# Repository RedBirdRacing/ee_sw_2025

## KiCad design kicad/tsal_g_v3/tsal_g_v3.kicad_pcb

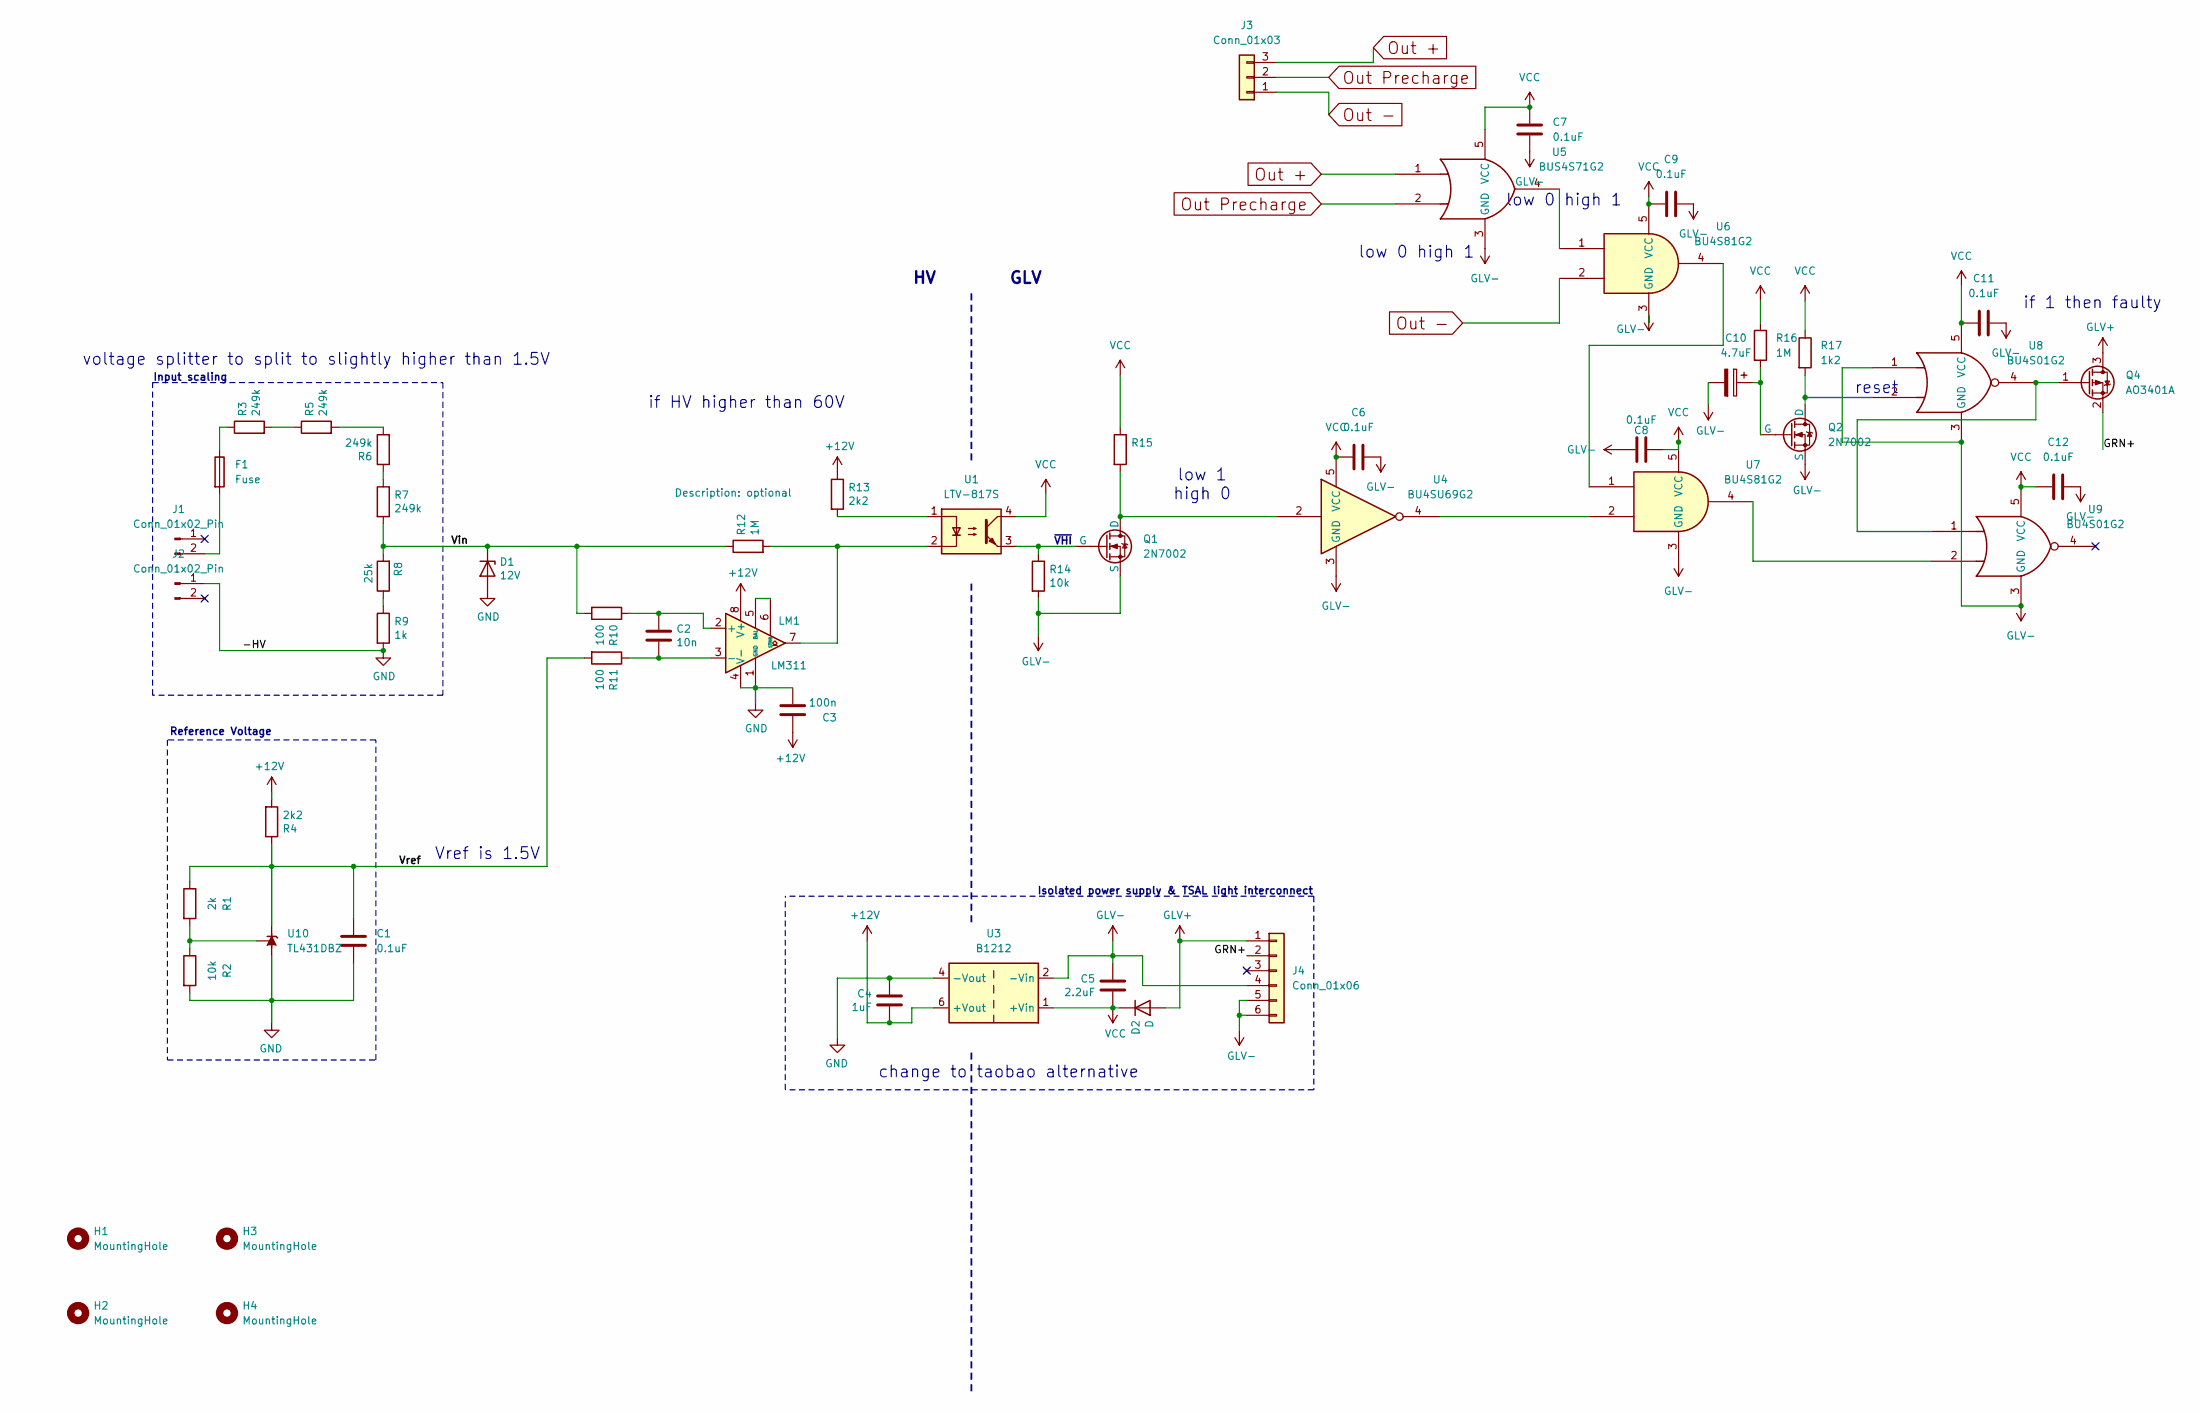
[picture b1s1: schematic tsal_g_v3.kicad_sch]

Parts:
C1, C6, C7, C8, C9, C11, C12: 0.1uF; C_0805_2012Metric_Pad1.18x1.45mm_HandSolder
C2: 10n; C_0805_2012Metric_Pad1.18x1.45mm_HandSolder
C3: 100n; C_0805_2012Metric_Pad1.18x1.45mm_HandSolder
C4: 1uF; C_0805_2012Metric_Pad1.18x1.45mm_HandSolder
C5: 2.2uF; C_0805_2012Metric_Pad1.18x1.45mm_HandSolder
C10: 4.7uF; C_0805_2012Metric_Pad1.18x1.45mm_HandSolder
D1: 12V; D_DO-35_SOD27_P7.62mm_Horizontal
D2: D; D_SMA
F1: Fuse; Fuse_0805_2012Metric_Pad1.15x1.40mm_HandSolder
H1, H2, H3, H4: MountingHole; MountingHole_3.2mm_M3
J1, J2: Conn_01x02_Pin; AMASS_XT60-M_1x02_P7.20mm_Vertical
J3: Conn_01x03; JST_VH_B3P-VH_1x03_P3.96mm_Vertical
J4: Conn_01x06; JST_VH_B6P-VH_1x06_P3.96mm_Vertical
LM1: LM311; SOIC-8_3.9x4.9mm_P1.27mm
Q1, Q2: 2N7002; SOT-23_Handsoldering
Q4: AO3401A; SOT-23_Handsoldering
R1: 2k; R_0805_2012Metric_Pad1.20x1.40mm_HandSolder
R2, R14: 10k; R_0805_2012Metric_Pad1.20x1.40mm_HandSolder
R3, R5, R6, R7: 249k; R_0805_2012Metric_Pad1.20x1.40mm_HandSolder
R4, R13: 2k2; R_0805_2012Metric_Pad1.20x1.40mm_HandSolder
R8: 25k; R_0805_2012Metric_Pad1.20x1.40mm_HandSolder
R9: 1k; R_0805_2012Metric_Pad1.20x1.40mm_HandSolder
R10, R11: 100; R_0805_2012Metric_Pad1.20x1.40mm_HandSolder
R12, R16: 1M; R_0805_2012Metric_Pad1.20x1.40mm_HandSolder
R15: R_0805_2012Metric_Pad1.20x1.40mm_HandSolder
R17: 1k2; R_0805_2012Metric_Pad1.20x1.40mm_HandSolder
U1: LTV-817S; SMDIP-4_W9.53mm
U3: B1212; Converter_DCDC_TRACO_TBA2-xxxx_Single_THT
U4: BU4SU69G2; SOT-23-5_HandSoldering
U5: BUS4S71G2; SOT-23-5_HandSoldering
U6, U7: BU4S81G2; SOT-23-5_HandSoldering
U8, U9: BU4S01G2; SOT-23-5_HandSoldering
U10: TL431DBZ; SOT-23_Handsoldering

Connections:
+12V: C3.1, C4.2, LM1.8 (V+), R4.2, R13.1, U3.6 (+Vout)
/GRN+: J4.2, Q4.2 (S)
/Vin: D1.1 (K), R7.2, R8.2, R10.2, R12.1
/Vref: C1.1, R1.1, R4.1, R11.2, U10.1 (K)
GLV+: D2.2 (A), J4.1, Q4.3 (D)
GLV-: C5.1, C6.1, C7.1, C8.1, C9.1, C10.2, C11.1, C12.1, J4.4, J4.5, J4.6, Q1.3 (S), Q2.3 (S), R14.2, U3.2 (-Vin), U4.3 (GND), U5.3 (GND), U6.3 (GND), U7.3 (GND), U8.1, U8.3 (GND), U9.3 (GND)
GND: C1.2, C3.2, C4.1, D1.2 (A), J2.1, LM1.1 (GND), LM1.4 (V-), R2.2, R9.2, U3.4 (-Vout), U10.3 (A)
unnamed: F1.1, R3.1
unnamed: F1.2, J1.2
unnamed: C2.1, LM1.2 (+), R10.1
unnamed: C2.2, LM1.3 (-), R11.1
unnamed: LM1.5 (BAL), LM1.6 (STRB)
unnamed: LM1.7, R12.2, U1.2
unnamed: Q1.1 (D), R15.2, U4.2
unnamed: Q1.2 (G), R14.1, U1.3
unnamed: Q2.1 (D), R17.2, U8.2
unnamed: C10.1, Q2.2 (G), R16.2
unnamed: Q4.1 (G), U8.4, U9.1
unnamed: R3.2, R5.1
unnamed: R5.2, R6.2
unnamed: R6.1, R7.1
unnamed: R8.1, R9.1
unnamed: R13.2, U1.1
unnamed: U4.4, U7.2
unnamed: U5.4, U6.1
unnamed: U6.4, U7.1
unnamed: U7.4, U9.2
unnamed: R1.2, R2.1, U10.2 (REF)
Out +: J3.3, U5.1
Out -: J3.1, U6.2
Out Precharge: J3.2, U5.2
VCC: C5.2, C6.2, C7.2, C8.2, C9.2, C11.2, C12.2, D2.1 (K), R15.1, R16.1, R17.1, U1.4, U3.1 (+Vin), U4.5 (VCC), U5.5 (VCC), U6.5 (VCC), U7.5 (VCC), U8.5 (VCC), U9.5 (VCC)

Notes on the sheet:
low 1 high 0
reset
~{VHI}
Isolated power supply & TSAL light interconnect
Input scaling
if 1 then faulty
GLV
Vref is 1.5V
low 0 high 1
if HV higher than 60V
Reference Voltage
voltage splitter to split to slightly higher than 1.5V
change to taobao alternative

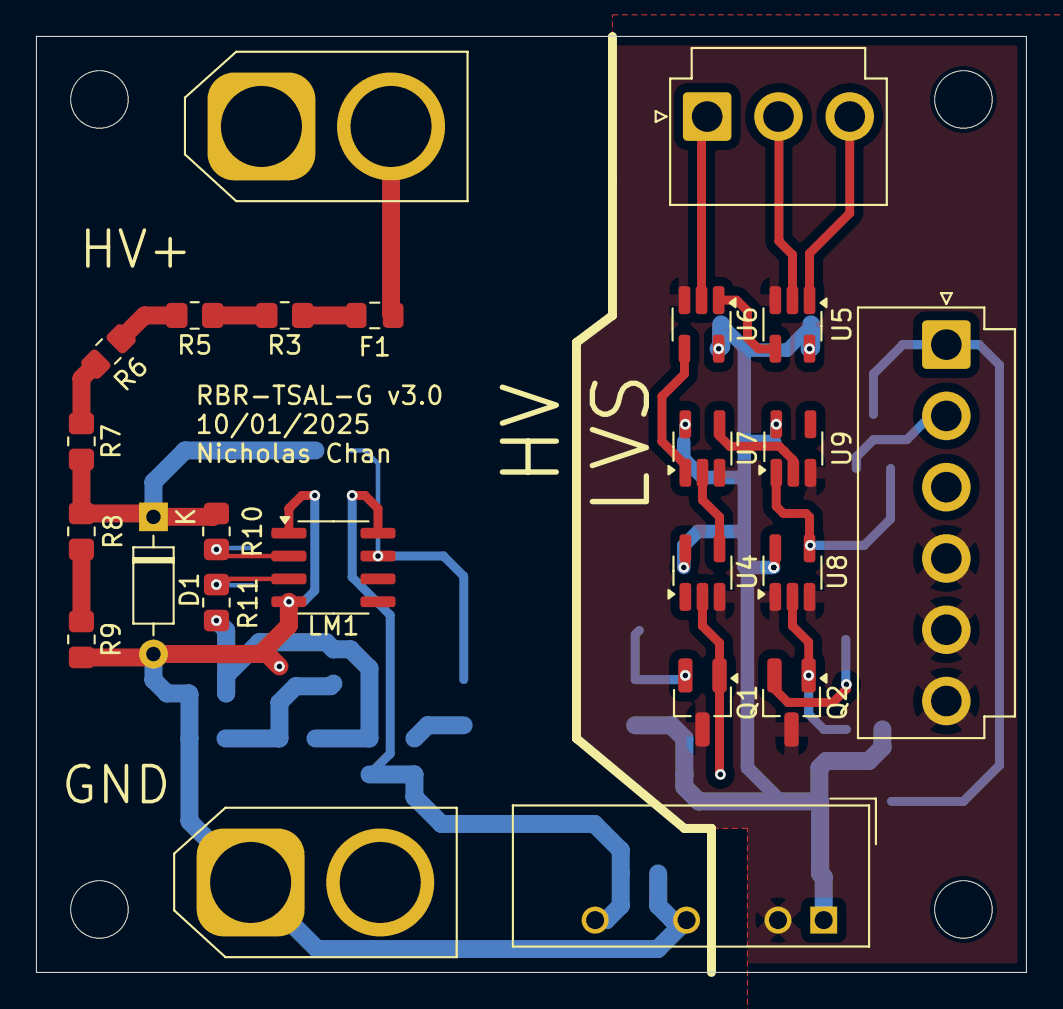
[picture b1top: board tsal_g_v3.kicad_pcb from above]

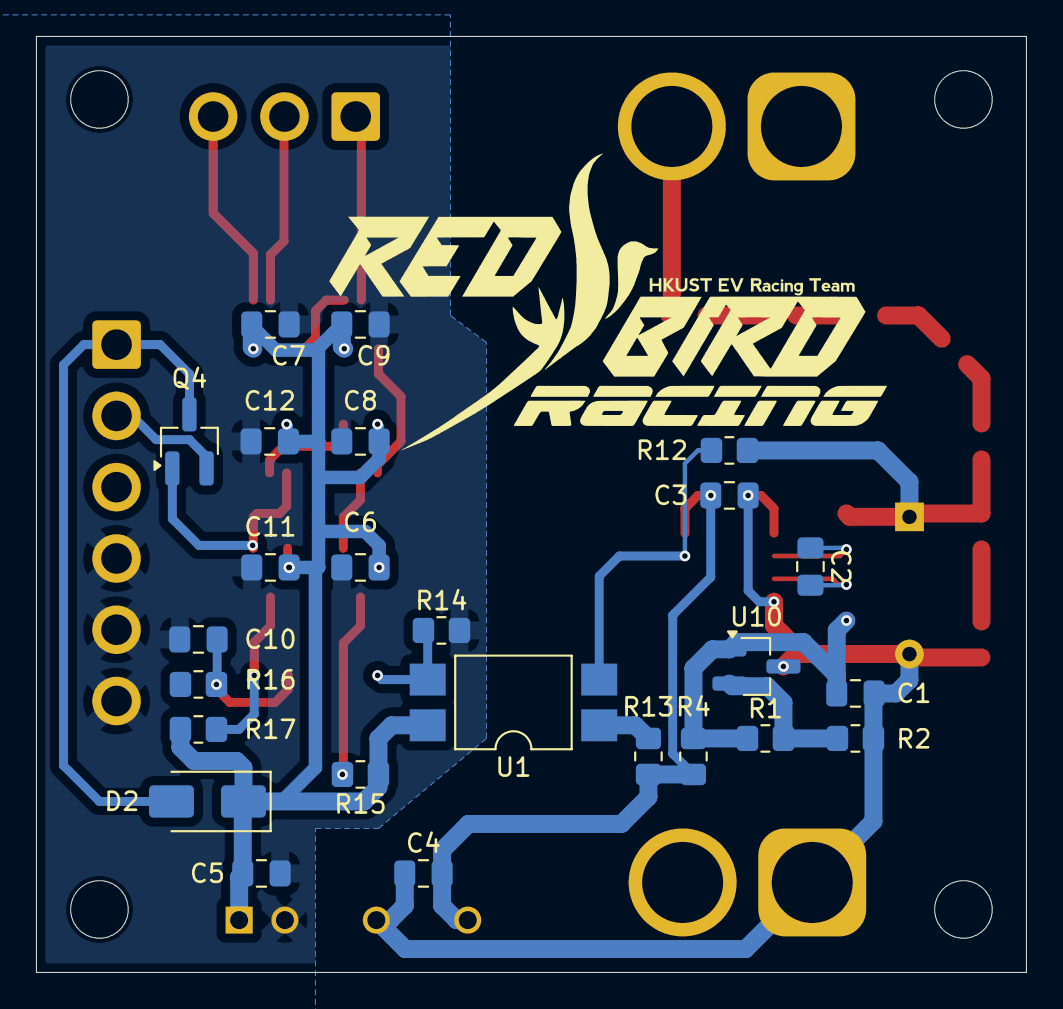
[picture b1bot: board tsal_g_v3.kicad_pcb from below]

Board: 2 copper layers, 55.0 x 52.0 mm, 53 parts (25 on the bottom side), 32 nets.

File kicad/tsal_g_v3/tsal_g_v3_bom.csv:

"Reference","Value","Footprint","Qty"
"C1,C6,C7,C8,C9,C11,C12","0.1uF","Capacitor_SMD:C_0805_2012Metric_Pad1.18x1.45mm_HandSolder","7"
"C2","10n","Capacitor_SMD:C_0805_2012Metric_Pad1.18x1.45mm_HandSolder","1"
"C3","100n","Capacitor_SMD:C_0805_2012Metric_Pad1.18x1.45mm_HandSolder","1"
"C4","1uF","Capacitor_SMD:C_0805_2012Metric_Pad1.18x1.45mm_HandSolder","1"
"C5","2.2uF","Capacitor_SMD:C_0805_2012Metric_Pad1.18x1.45mm_HandSolder","1"
"C10","4.7uF","Capacitor_SMD:C_0805_2012Metric_Pad1.18x1.45mm_HandSolder","1"
"D1","12V","Diode_THT:D_DO-35_SOD27_P7.62mm_Horizontal","1"
"D2","D","Diode_SMD:D_SMA","1"
"F1","Fuse","Fuse:Fuse_0805_2012Metric_Pad1.15x1.40mm_HandSolder","1"
"J1,J2","Conn_01x02_Pin","Connector_AMASS:AMASS_XT60-M_1x02_P7.20mm_Vertical","2"
"J3","Conn_01x03","Connector_JST:JST_VH_B3P-VH_1x03_P3.96mm_Vertical","1"
"J4","Conn_01x06","Connector_JST:JST_VH_B6P-VH_1x06_P3.96mm_Vertical","1"
"LM1","LM311","Package_SO:SOIC-8_3.9x4.9mm_P1.27mm","1"
"Q1,Q2","2N7002","Package_TO_SOT_SMD:SOT-23_Handsoldering","2"
"Q4","AO3401A","Package_TO_SOT_SMD:SOT-23_Handsoldering","1"
"R1","2k","Resistor_SMD:R_0805_2012Metric_Pad1.20x1.40mm_HandSolder","1"
"R2,R14","10k","Resistor_SMD:R_0805_2012Metric_Pad1.20x1.40mm_HandSolder","2"
"R3,R5,R6,R7","249k","Resistor_SMD:R_0805_2012Metric_Pad1.20x1.40mm_HandSolder","4"
"R4,R13","2k2","Resistor_SMD:R_0805_2012Metric_Pad1.20x1.40mm_HandSolder","2"
"R8","25k","Resistor_SMD:R_0805_2012Metric_Pad1.20x1.40mm_HandSolder","1"
"R9","1k","Resistor_SMD:R_0805_2012Metric_Pad1.20x1.40mm_HandSolder","1"
"R10,R11","100","Resistor_SMD:R_0805_2012Metric_Pad1.20x1.40mm_HandSolder","2"
"R12,R16","1M","Resistor_SMD:R_0805_2012Metric_Pad1.20x1.40mm_HandSolder","2"
"R15","~","Resistor_SMD:R_0805_2012Metric_Pad1.20x1.40mm_HandSolder","1"
"R17","1k2","Resistor_SMD:R_0805_2012Metric_Pad1.20x1.40mm_HandSolder","1"
"U1","LTV-817S","Package_DIP:SMDIP-4_W9.53mm","1"
"U3","B1212","Converter_DCDC:Converter_DCDC_TRACO_TBA2-xxxx_Single_THT","1"
"U4","BU4SU69G2","Package_TO_SOT_SMD:SOT-23-5_HandSoldering","1"
"U5","BUS4S71G2","Package_TO_SOT_SMD:SOT-23-5_HandSoldering","1"
"U6,U7","BU4S81G2 ","Package_TO_SOT_SMD:SOT-23-5_HandSoldering","2"
"U8,U9","BU4S01G2","Package_TO_SOT_SMD:SOT-23-5_HandSoldering","2"
"U10","TL431DBZ","Package_TO_SOT_SMD:SOT-23_Handsoldering","1"

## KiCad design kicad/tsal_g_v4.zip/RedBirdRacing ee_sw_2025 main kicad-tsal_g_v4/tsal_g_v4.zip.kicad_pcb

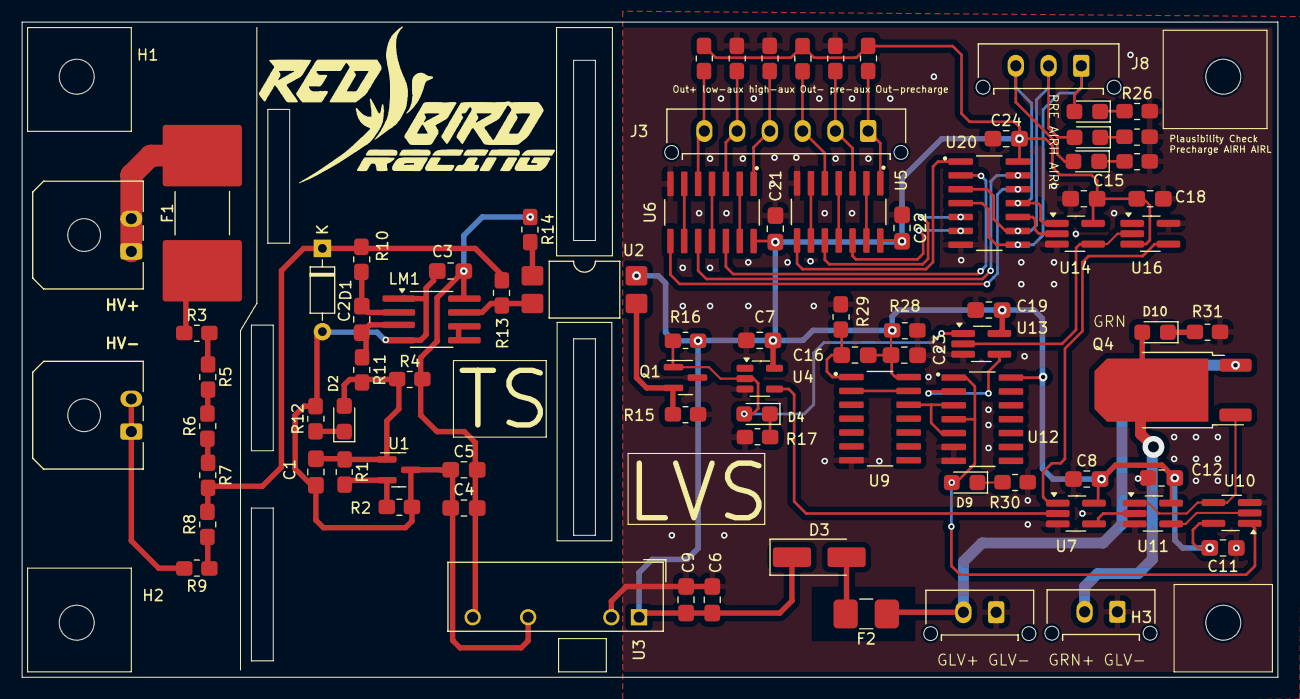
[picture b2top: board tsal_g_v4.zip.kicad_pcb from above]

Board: 2 copper layers, 115.0 x 60.0 mm, 89 parts (1 on the bottom side), 64 nets.

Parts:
C1, C5, C7, C8, C11, C12, C15, C16, C17, C18, C19, C21, C22, C23, C24: 0.1uF; C_0805_2012Metric_Pad1.18x1.45mm_HandSolder_L
C2: 10n; C_0805_2012Metric_Pad1.18x1.45mm_HandSolder_L
C3: 100n; C_0805_2012Metric_Pad1.18x1.45mm_HandSolder_L
C4: 1uF; C_0805_2012Metric_Pad1.18x1.45mm_HandSolder_L
C6: 2.2uF; C_0805_2012Metric_Pad1.18x1.45mm_HandSolder_L
C9: 100nF; C_0805_2012Metric_Pad1.18x1.45mm_HandSolder_L
D1: 12V; D_DO-35_SOD27_P7.62mm_Horizontal
D2, D4, D5, D6, D7, D9, D10: LED; LED_0805_2012Metric_Pad1.45x1.40mm_HandSolder
D3: D; D_SMA_Handsoldering
F1: Fuse; Fuse_Littelfuse-NANO2-885
F2: Fuse; Fuse_1210_3225Metric_Pad1.42x2.65mm_HandSolder
H1, H2, H3, H4: MountingHole; MountingHole_3.2mm_M3
J1, J2: Conn_01x02_Pin; Molex_Micro-Fit_3.0_43650-0200_1x02_P3.00mm_Horizontal
J3: Conn_01x06_Pin; Molex_Micro-Fit_3.0_43650-0615_1x06_P3.00mm_Vertical
J6, J7: Conn_01x02_Pin; Molex_Micro-Fit_3.0_43650-0215_1x02_P3.00mm_Vertical
J8: Conn_01x03; Molex_Micro-Fit_3.0_43650-0315_1x03_P3.00mm_Vertical
LM1: LM311; SOIC-8_3.9x4.9mm_P1.27mm_RMC_Handsolder
Q1: 2N7002; SOT-23
Q4: QM6015D; TO-252-2
R1: 2k; R_0805_2012Metric_Pad1.20x1.40mm_HandSolder_L
R2, R15, R18, R19, R20, R21, R22, R23, R28: 10k; R_0805_2012Metric_Pad1.20x1.40mm_HandSolder_L
R3, R5, R6, R7: 249k; R_0805_2012Metric_Pad1.20x1.40mm_HandSolder_L
R4, R14: 2k2; R_0805_2012Metric_Pad1.20x1.40mm_HandSolder_L
R8: 25k; R_0805_2012Metric_Pad1.20x1.40mm_HandSolder_L
R9, R12, R17, R24, R25, R26, R30, R31: 1k; R_0805_2012Metric_Pad1.20x1.40mm_HandSolder_L
R10, R11: 100; R_0805_2012Metric_Pad1.20x1.40mm_HandSolder_L
R13: 1M; R_0805_2012Metric_Pad1.20x1.40mm_HandSolder_L
R16: 22k; R_0805_2012Metric_Pad1.20x1.40mm_HandSolder_L
R29: 100k; R_0805_2012Metric_Pad1.20x1.40mm_HandSolder_L
U1: TL431DBZ; SOT-23
U2: LTV-817S; SMDIP-4_W9.53mm
U3: B1212; Converter_DCDC_F1212
U4: BU4SU69G2; SOT-23-5_HandSoldering
U5, U6, U9: 40106; SOIC127P600X175-14N
U7: BU4S81G2; SOT-23-5_HandSoldering_Extended_RMC
U10, U11: BU4S01G2; SOT-23-5_HandSoldering_Extended_RMC
U12: 4077; SOIC127P600X175-14N
U13: BU4S71G2; SOT-23-5_HandSoldering_Extended_RMC
U14: BUS4S71G2; SOT-23-5_HandSoldering_Extended_RMC
U16: BU4SU69G2; SOT-23-5_HandSoldering_Extended_RMC
U20: 4071; SOIC127P600X175-14N

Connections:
+12V: C3.1, C4.2, C5.2, LM1.8 (V+), R4.2, R14.1, U3.6 (+Vout)
/-HV: J2.1, J2.2, R9.2
/GRN+: D10.2 (A), J6.2, Q4.2 (D)
/Vin: D1.1 (K), R7.2, R8.2, R10.2, R13.1
/Vref: C1.1, D2.2 (A), R1.1, R4.1, R11.2, U1.1 (K)
AIRH Check: D6.2 (A), J8.2, U20.3, U20.9
AIRL Check: D5.2 (A), J8.3, U14.1, U20.11
GLV+: F2.1, J7.2, Q4.3 (S)
GLV-: C6.1, C7.1, C8.1, C9.1, C11.1, C12.1, C15.1, C17.1, C18.1, C19.2, C21.1, C22.1, C23.1, C24.1, J6.1, J7.1, Q1.3 (S), R15.2, R17.2, R20.2, R21.2, R23.2, R24.2, R25.2, R26.2, R28.2, R29.2, R30.2, R31.2, U3.2 (-Vin), U4.3 (GND), U5.7 (VSS), U6.7 (VSS), U7.3 (GND), U9.7 (VSS), U10.3 (GND), U11.3 (GND), U12.6, U12.7 (VSS), U13.3 (GND), U14.3 (GND), U16.5 (VCC), U20.7 (VSS)
GND: C1.2, C3.2, C4.1, C5.1, D1.2 (A), LM1.1 (GND), LM1.4 (V-), R2.2, R12.2, U1.3 (A), U3.4 (-Vout)
unnamed: C16.2, R29.1, U9.1
unnamed: D2.1 (K), R12.1
unnamed: D3.2 (A), F2.2
unnamed: D4.1 (K), R17.1
unnamed: D5.1 (K), R25.1
unnamed: D6.1 (K), R24.1
unnamed: D7.1 (K), R26.1
unnamed: D9.1 (K), R30.1
unnamed: D10.1 (K), R31.1
unnamed: F1.1, R3.1
unnamed: F1.2, J1.1, J1.2
unnamed: J3.1, R19.1, U5.1
unnamed: J3.2, R20.1, U5.3
unnamed: J3.3, R18.1, U5.5
unnamed: J3.4, R23.1, U6.1
unnamed: J3.5, R21.1, U6.3
unnamed: J3.6, R22.1, U6.5
unnamed: C2.1, LM1.2 (+), R10.1
unnamed: C2.2, LM1.3 (-), R11.1
unnamed: LM1.5 (BAL), LM1.6 (STRB)
unnamed: LM1.7, R13.2, U2.2
unnamed: Q1.2 (G), R15.1, U2.3
unnamed: Q4.1 (G), U10.4, U11.1
unnamed: R3.2, R5.1
unnamed: R5.2, R6.2
unnamed: R6.1, R7.1
unnamed: R8.1, R9.1
unnamed: R14.2, U2.1
unnamed: R1.2, R2.1, U1.2 (REF)
unnamed: U5.6, U5.9
unnamed: U5.4, U5.11
unnamed: U5.2, U5.13
unnamed: U6.6, U6.9
unnamed: U6.4, U6.11
unnamed: U6.2, U6.13
unnamed: U9.2, U9.13
unnamed: U10.2, U11.4
unnamed: U7.4, U11.2
unnamed: U12.2, U13.4
unnamed: U9.12, U12.3, U12.5
unnamed: U14.2, U20.10
Out +: U6.8, U20.12
Out -: U5.8, U20.1
Out Precharge: U5.12, U20.6
Precharge Check: D7.2 (A), J8.1, U20.4, U20.8
RELAY LOGIC: U7.1, U16.4
RELAY RESET: U13.2, U14.4, U16.2
RESET: D9.2 (A), U10.1, U12.1, U12.4
TS LOGIC: U4.4, U7.2
TS RESET: D4.2 (A), Q1.1 (D), R16.2, U4.2, U13.1
VCC: C6.2, C7.2, C8.2, C9.2, C11.2, C12.2, C15.2, C16.1, C17.2, C18.2, C19.1, C21.2, C22.2, C23.2, C24.2, D3.1 (K), R16.1, R18.2, R19.2, R22.2, R28.1, U2.4, U3.1 (+Vin), U4.5 (VCC), U5.14 (VDD), U6.14 (VDD), U7.5 (VCC), U9.14 (VDD), U10.5 (VCC), U11.5 (VCC), U12.14 (VDD), U13.5 (VCC), U14.5 (VCC), U16.3 (GND), U20.14 (VDD)
high aux: U6.12, U20.2
low aux: U6.10, U20.13
pre aux: U5.10, U20.5

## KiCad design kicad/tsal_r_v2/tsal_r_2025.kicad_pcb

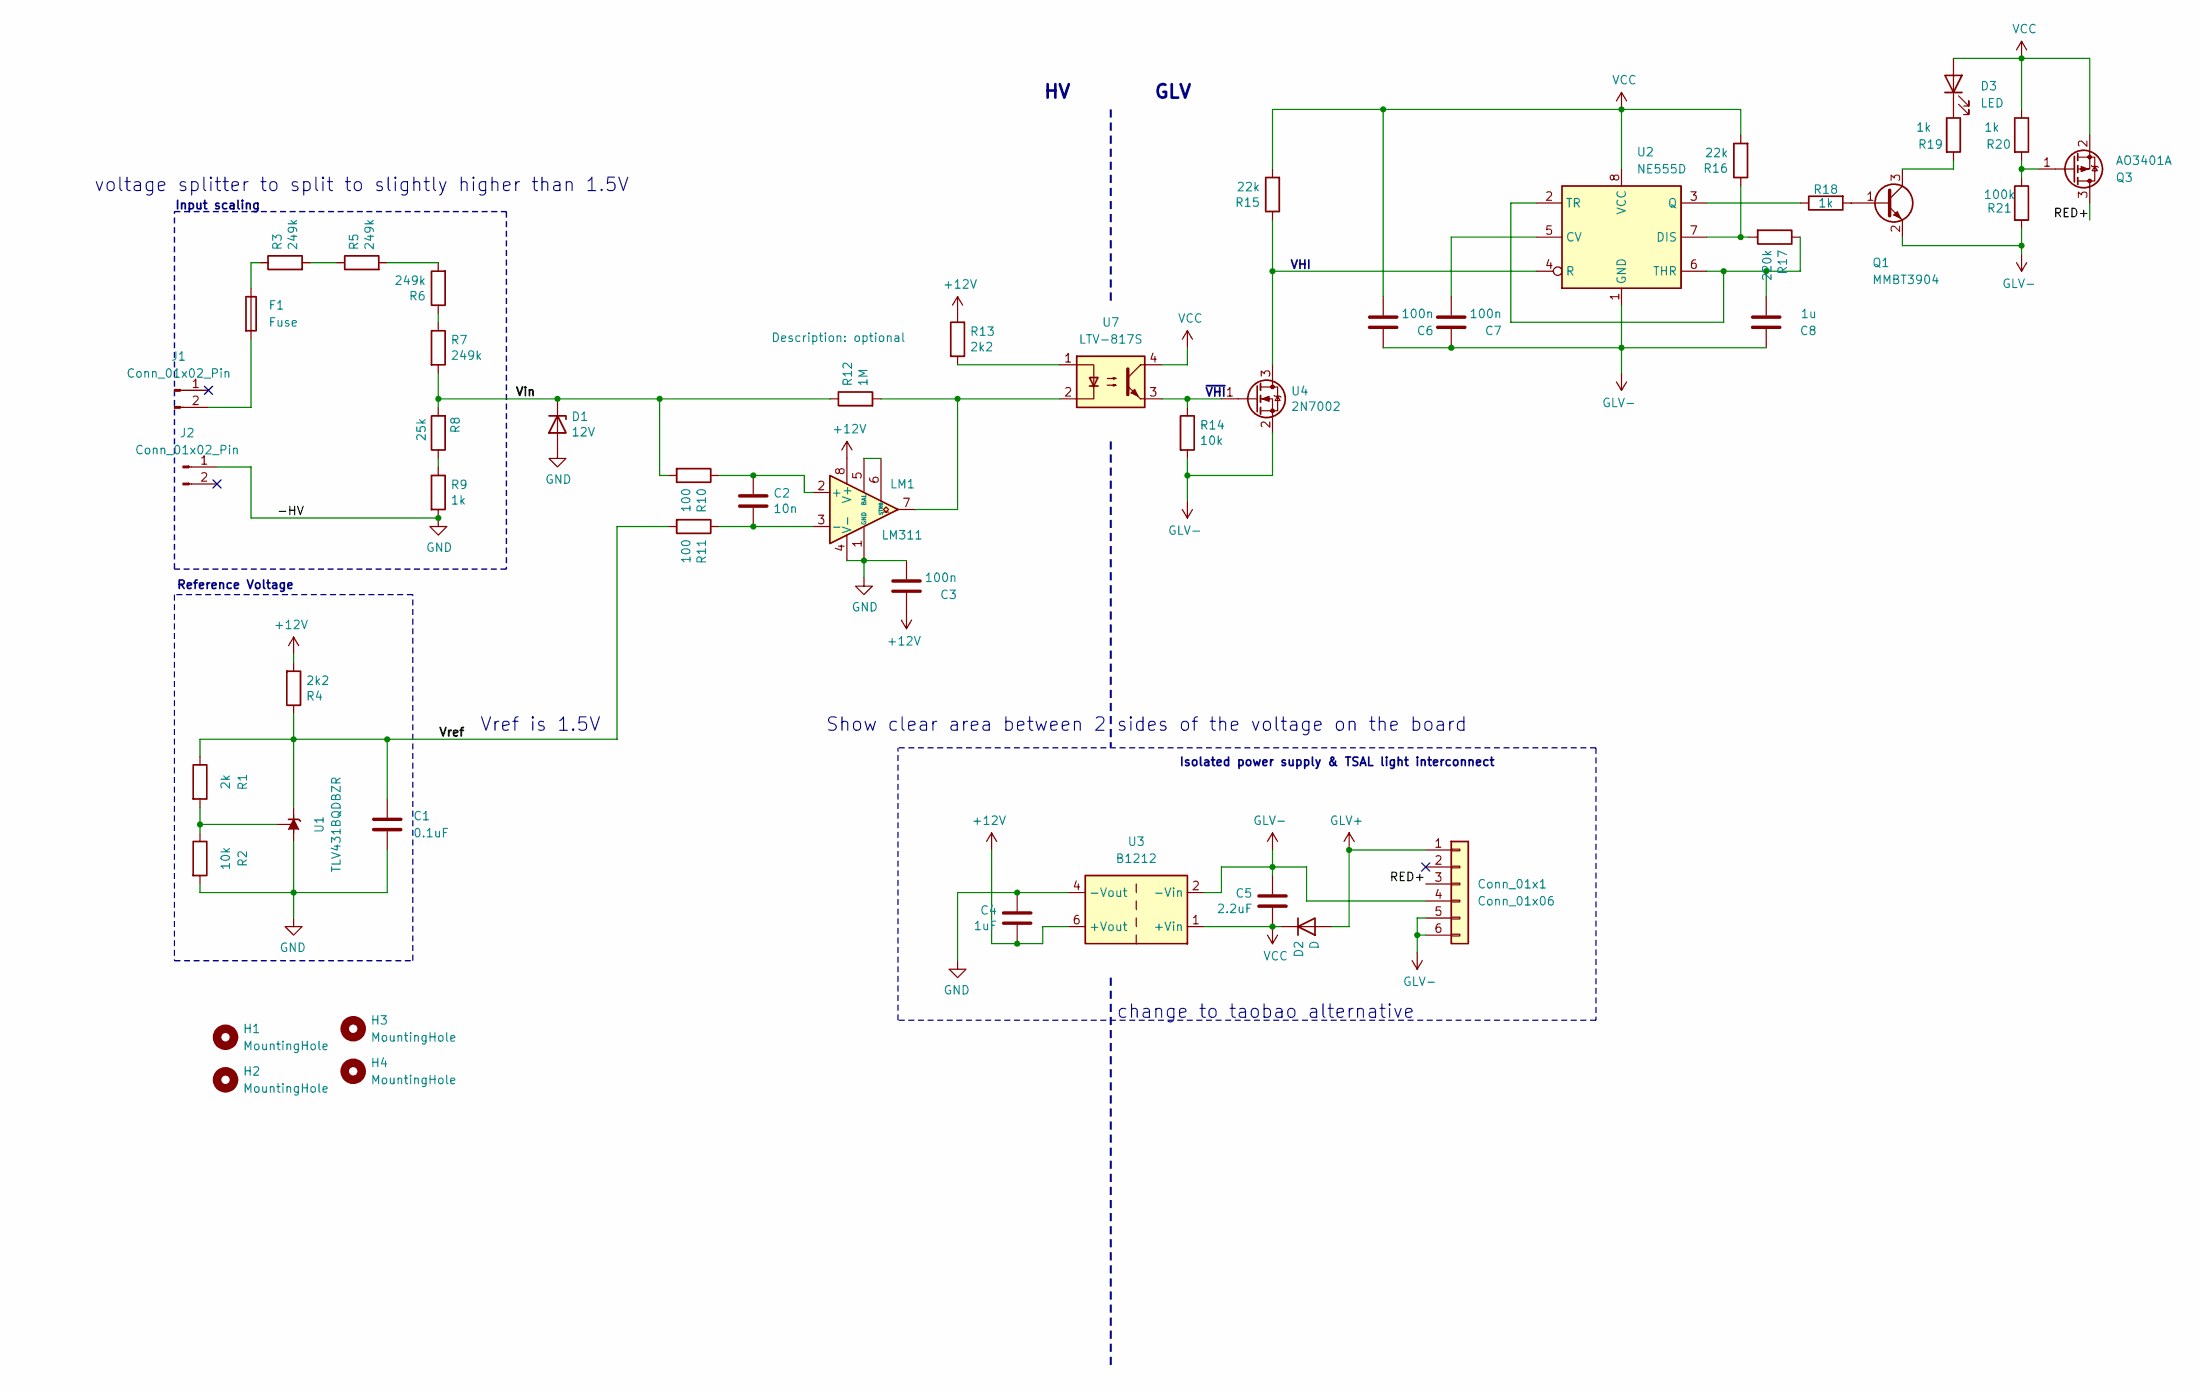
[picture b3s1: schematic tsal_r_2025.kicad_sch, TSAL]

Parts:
C1: 0.1uF; C_0805_2012Metric_Pad1.18x1.45mm_HandSolder
C2: 10n; C_0805_2012Metric_Pad1.18x1.45mm_HandSolder
C3, C6, C7: 100n; C_0805_2012Metric_Pad1.18x1.45mm_HandSolder
C4: 1uF; C_0805_2012Metric_Pad1.18x1.45mm_HandSolder
C5: 2.2uF; C_0805_2012Metric_Pad1.18x1.45mm_HandSolder
C8: 1u; C_0805_2012Metric_Pad1.18x1.45mm_HandSolder
Conn_01x1: Conn_01x06; JST_VH_B6P-VH_1x06_P3.96mm_Vertical
D1: 12V; D_DO-35_SOD27_P7.62mm_Horizontal
D2: D; D_SMA
D3: LED; LED_0805_2012Metric_Pad1.15x1.40mm_HandSolder
F1: Fuse; Fuse_0805_2012Metric_Pad1.15x1.40mm_HandSolder
H1, H2, H3, H4: MountingHole; MountingHole_3.2mm_M3
J1, J2: Conn_01x02_Pin; AMASS_XT60-M_1x02_P7.20mm_Vertical
LM1: LM311; SOIC-8_3.9x4.9mm_P1.27mm
Q1: MMBT3904; SOT-23_Handsoldering
Q3: AO3401A; SOT-23_Handsoldering
R1: 2k; R_0805_2012Metric_Pad1.20x1.40mm_HandSolder
R2, R14: 10k; R_0805_2012Metric_Pad1.20x1.40mm_HandSolder
R3, R5, R6, R7: 249k; R_0805_2012Metric_Pad1.20x1.40mm_HandSolder
R4, R13: 2k2; R_0805_2012Metric_Pad1.20x1.40mm_HandSolder
R8: 25k; R_0805_2012Metric_Pad1.20x1.40mm_HandSolder
R9, R18, R19, R20: 1k; R_0805_2012Metric_Pad1.20x1.40mm_HandSolder
R10, R11: 100; R_0805_2012Metric_Pad1.20x1.40mm_HandSolder
R12: 1M; R_0805_2012Metric_Pad1.20x1.40mm_HandSolder
R15, R16: 22k; R_0805_2012Metric_Pad1.20x1.40mm_HandSolder
R17: 220k; R_0805_2012Metric_Pad1.20x1.40mm_HandSolder
R21: 100k; R_0805_2012Metric_Pad1.20x1.40mm_HandSolder
U1: TLV431BQDBZR; SOT-23
U2: NE555D; SOIC-8_3.9x4.9mm_P1.27mm
U3: B1212; Converter_DCDC_TRACO_TBA2-xxxx_Single_THT
U4: 2N7002; SOT-23_Handsoldering
U7: LTV-817S; SMDIP-4_W9.53mm

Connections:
+12V: C3.1, C4.2, LM1.8 (V+), R4.2, R13.1, U3.6 (+Vout)
/RED+: Conn_01x1.3, Q3.3 (D)
/Vin: D1.1 (K), R7.2, R8.2, R10.2, R12.1
/Vref: C1.1, R1.1, R4.1, R11.2, U1.3 (K)
GLV+: Conn_01x1.1, D2.2 (A)
GLV-: C5.1, C6.1, C7.1, C8.1, Conn_01x1.4, Conn_01x1.5, Conn_01x1.6, Q1.2 (E), R14.2, R21.2, U2.1 (GND), U3.2 (-Vin), U4.2 (S)
GND: C1.2, C3.2, C4.1, D1.2 (A), J2.1, LM1.1 (GND), LM1.4 (V-), R2.2, R9.2, U1.2 (A), U3.4 (-Vout)
unnamed: D3.1 (K), R19.1
unnamed: F1.1, R3.1
unnamed: F1.2, J1.2
unnamed: C2.1, LM1.2 (+), R10.1
unnamed: C2.2, LM1.3 (-), R11.1
unnamed: LM1.5 (BAL), LM1.6 (STRB)
unnamed: LM1.7, R12.2, U7.2
unnamed: Q1.1 (B), R18.2
unnamed: Q1.3 (C), R19.2
unnamed: Q3.1 (G), R20.2, R21.1
unnamed: R3.2, R5.1
unnamed: R5.2, R6.2
unnamed: R6.1, R7.1
unnamed: R8.1, R9.1
unnamed: R13.2, U7.1
unnamed: R1.2, R2.1, U1.1 (REF)
unnamed: C7.2, U2.5 (CV)
unnamed: R16.1, R17.2, U2.7 (DIS)
unnamed: R18.1, U2.3 (Q)
unnamed: R15.1, U2.4 (R), U4.3 (D)
unnamed: C8.2, R17.1, U2.2 (TR), U2.6 (THR)
unnamed: R14.1, U4.1 (G), U7.3
VCC: C5.2, C6.2, D2.1 (K), D3.2 (A), Q3.2 (S), R15.2, R16.2, R20.1, U2.8 (VCC), U3.1 (+Vin), U7.4

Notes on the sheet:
change to taobao alternative
voltage splitter to split to slightly higher than 1.5V
Show clear area between 2 sides of the voltage on the board
Isolated power supply & TSAL light interconnect
Reference Voltage
~{VHI}
Input scaling
GLV
VHI
Vref is 1.5V

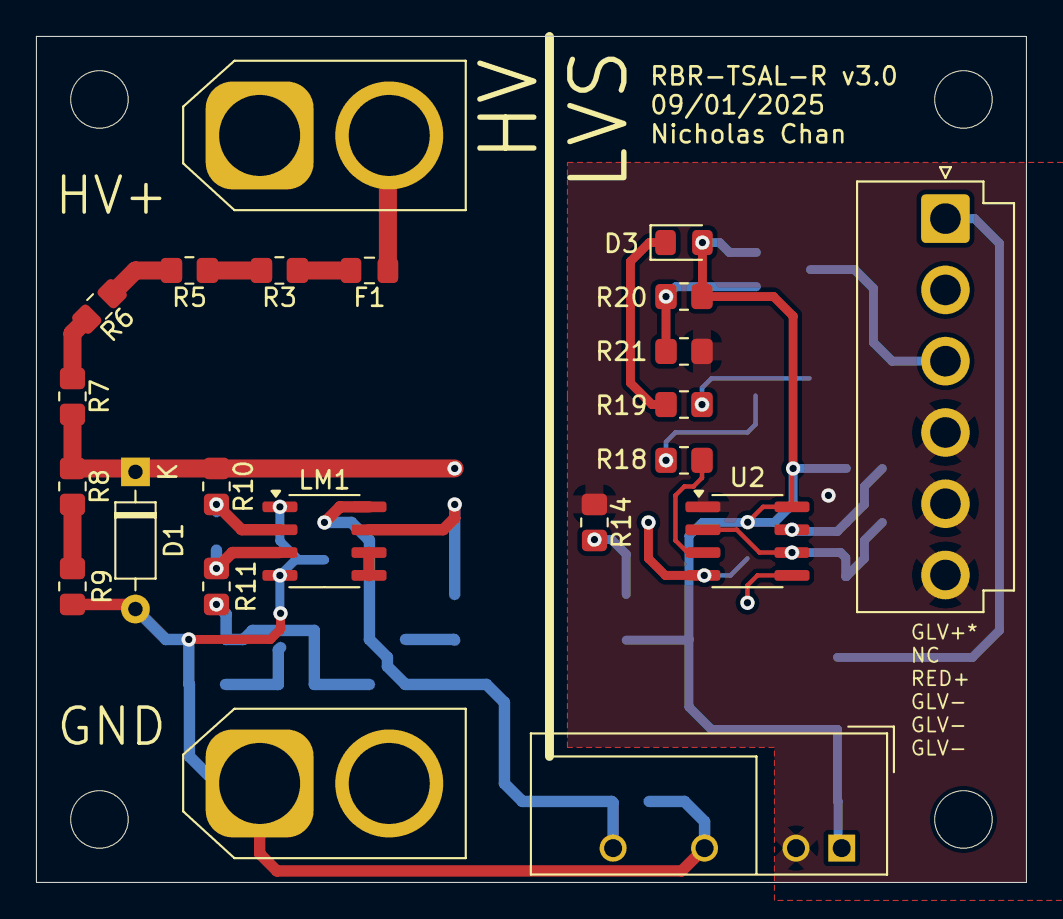
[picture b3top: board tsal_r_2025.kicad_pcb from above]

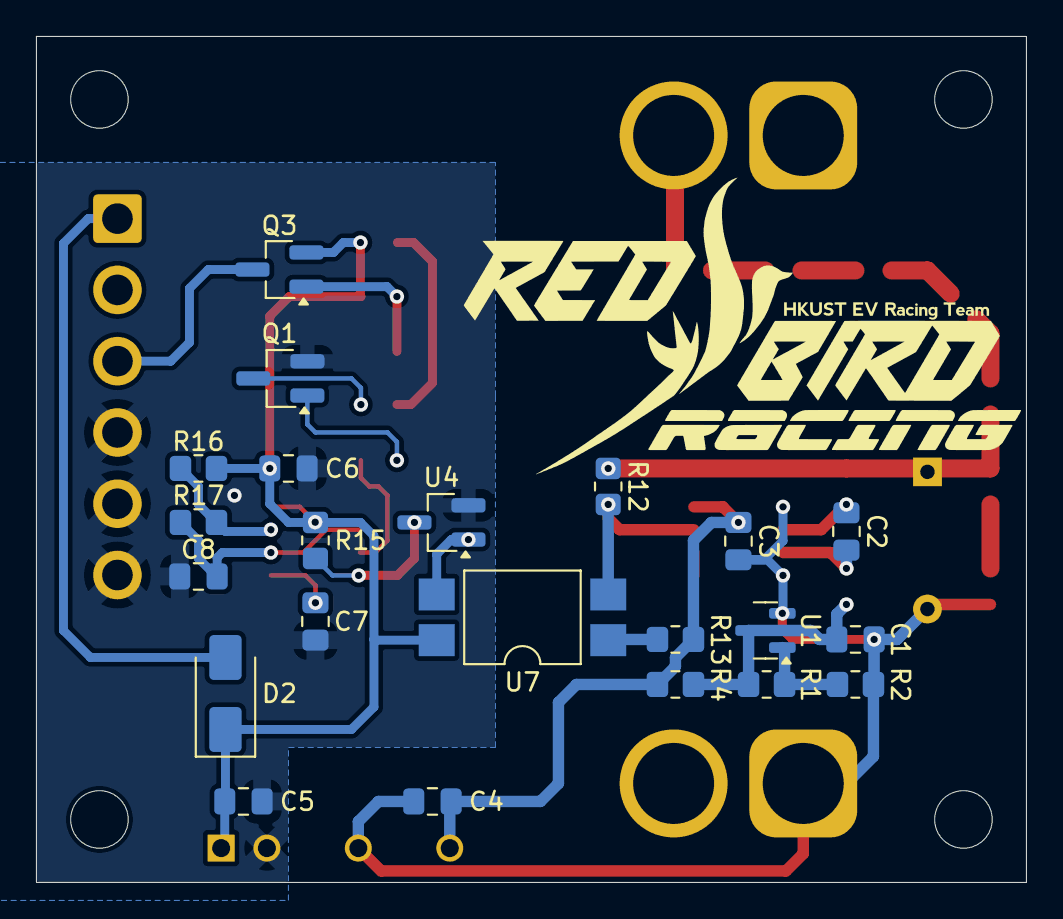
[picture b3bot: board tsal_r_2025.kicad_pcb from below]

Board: 2 copper layers, 55.0 x 47.0 mm, 48 parts (22 on the bottom side), 30 nets.

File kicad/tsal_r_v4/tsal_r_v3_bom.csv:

"Reference","Value","Footprint","Qty"
"C1","0.1uF","Capacitor_SMD:C_0805_2012Metric_Pad1.18x1.45mm_HandSolder","1"
"C2","10n","Capacitor_SMD:C_0805_2012Metric_Pad1.18x1.45mm_HandSolder","1"
"C3,C6,C7","100n","Capacitor_SMD:C_0805_2012Metric_Pad1.18x1.45mm_HandSolder","3"
"C4","1uF","Capacitor_SMD:C_0805_2012Metric_Pad1.18x1.45mm_HandSolder","1"
"C5","2.2uF","Capacitor_SMD:C_0805_2012Metric_Pad1.18x1.45mm_HandSolder","1"
"C8","1u","Capacitor_SMD:C_0805_2012Metric_Pad1.18x1.45mm_HandSolder","1"
"Conn_01x1","Conn_01x06","Connector_JST:JST_VH_B6P-VH_1x06_P3.96mm_Vertical","1"
"D1","12V","Diode_THT:D_DO-35_SOD27_P7.62mm_Horizontal","1"
"D2","D","Diode_SMD:D_SMA_Handsoldering","1"
"D3","LED","LED_SMD:LED_0805_2012Metric_Pad1.15x1.40mm_HandSolder","1"
"F1","Fuse","Fuse:Fuse_0805_2012Metric_Pad1.15x1.40mm_HandSolder","1"
"J1,J2","Conn_01x02_Pin","Connector_AMASS:AMASS_XT60-M_1x02_P7.20mm_Vertical","2"
"LM1","LM311","Package_SO:SOIC-8_3.9x4.9mm_P1.27mm","1"
"Q1","MMBT3904","Package_TO_SOT_SMD:SOT-23_Handsoldering","1"
"Q3","AO3401A","Package_TO_SOT_SMD:SOT-23_Handsoldering","1"
"R1","2k","Resistor_SMD:R_0805_2012Metric_Pad1.20x1.40mm_HandSolder","1"
"R2,R14","10k","Resistor_SMD:R_0805_2012Metric_Pad1.20x1.40mm_HandSolder","2"
"R3,R5,R6,R7","249k","Resistor_SMD:R_0805_2012Metric_Pad1.20x1.40mm_HandSolder","4"
"R4,R13","2k2","Resistor_SMD:R_0805_2012Metric_Pad1.20x1.40mm_HandSolder","2"
"R8","25k","Resistor_SMD:R_0805_2012Metric_Pad1.20x1.40mm_HandSolder","1"
"R9,R18,R19,R20","1k","Resistor_SMD:R_0805_2012Metric_Pad1.20x1.40mm_HandSolder","4"
"R10,R11","100","Resistor_SMD:R_0805_2012Metric_Pad1.20x1.40mm_HandSolder","2"
"R12","1M","Resistor_SMD:R_0805_2012Metric_Pad1.20x1.40mm_HandSolder","1"
"R15,R16","22k","Resistor_SMD:R_0805_2012Metric_Pad1.20x1.40mm_HandSolder","2"
"R17","220k","Resistor_SMD:R_0805_2012Metric_Pad1.20x1.40mm_HandSolder","1"
"R21","100k","Resistor_SMD:R_0805_2012Metric_Pad1.20x1.40mm_HandSolder","1"
"U1","TL431DBZ","Package_TO_SOT_SMD:SOT-23","1"
"U2","NE555D","Package_SO:SOIC-8_3.9x4.9mm_P1.27mm","1"
"U3","B1212","Converter_DCDC:Converter_DCDC_TRACO_TBA2-xxxx_Single_THT","1"
"U4","2N7002","Package_TO_SOT_SMD:SOT-23_Handsoldering","1"
"U7","LTV-817S","Package_DIP:SMDIP-4_W9.53mm","1"
